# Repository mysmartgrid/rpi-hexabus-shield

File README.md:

rpi-hexabus-shield
==================

This repository contains a plug-in antenna prototype for the raspberry platform.

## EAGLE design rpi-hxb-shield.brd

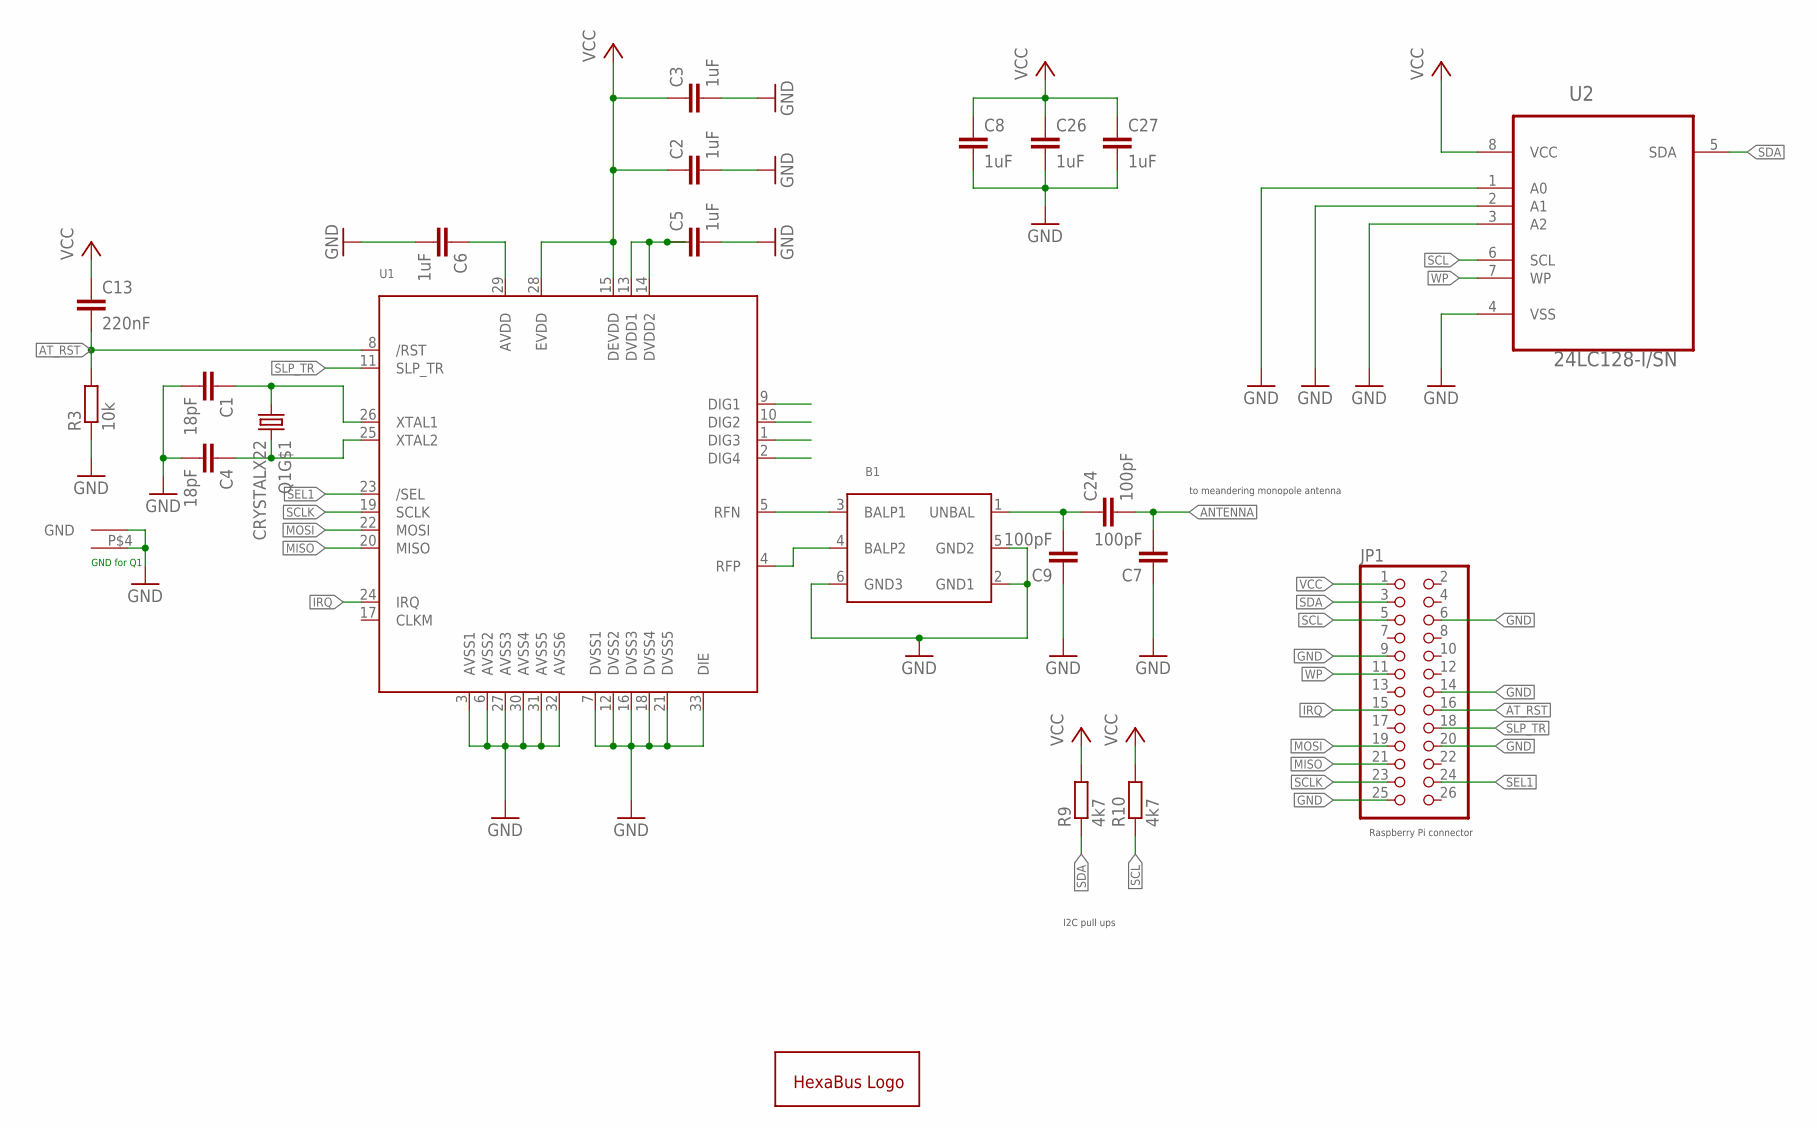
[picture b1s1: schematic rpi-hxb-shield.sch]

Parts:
B1: BALUN+LP; BALUN0805
C1, C4: 18pF; C0402K
C2, C3, C5, C6, C8, C26, C27: 1uF; C0402K
C7, C9, C24: 100pF; C0402K
C13: 220nF; C0402K
JP1: PINHD-2X13; 2X13
Q1: CRYSTALX22; X22
R3: 10k; R0402
R9, R10: 4k7; R0402
U1: AT86RF212; 32QN2
U2: 24LC128-I/SN; SOIC127P600X175-8N
U$1: HEXAKRAKE

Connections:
ANTENNA: C7.2, C24.2
AT_RST: C13.2, JP1.16, R3.2, U1.8 (/RST)
GND: B1.2 (GND1), B1.5 (GND2), B1.6 (GND3), C1.2, C2.2, C3.2, C4.2, C5.2, C6.2, C7.1, C8.2, C9.1, C26.2, C27.2, JP1.6, JP1.9, JP1.14, JP1.20, JP1.25, Q1.P$2 (GND), Q1.P$4 (GND1), R3.1, U1.3 (AVSS1), U1.6 (AVSS2), U1.7 (DVSS1), U1.12 (DVSS2), U1.16 (DVSS3), U1.18 (DVSS4), U1.21 (DVSS5), U1.27 (AVSS3), U1.30 (AVSS4), U1.31 (AVSS5), U1.32 (AVSS6), U1.33 (DIE), U2.1 (A0), U2.2 (A1), U2.3 (A2), U2.4 (VSS)
IRQ: JP1.15, U1.24 (IRQ)
MISO: JP1.21, U1.20 (MISO)
MOSI: JP1.19, U1.22 (MOSI)
unnamed: C6.1, U1.29 (AVDD)
unnamed: C5.1, U1.13 (DVDD1), U1.14 (DVDD2)
unnamed: B1.3 (BALP1), U1.5 (RFN)
unnamed: B1.4 (BALP2), U1.4 (RFP)
unnamed: C1.1, Q1.P$1 (1), U1.26 (XTAL1)
unnamed: C4.1, Q1.P$3 (2), U1.25 (XTAL2)
unnamed: B1.1 (UNBAL), C9.2, C24.1
SCL: JP1.5, R10.1, U2.6 (SCL)
SCLK: JP1.23, U1.19 (SCLK)
SDA: JP1.3, R9.1, U2.5 (SDA)
SEL1: JP1.24, U1.23 (/SEL)
SLP_TR: JP1.18, U1.11 (SLP_TR)
VCC: C2.1, C3.1, C8.1, C13.1, C26.1, C27.1, JP1.1, R9.2, R10.2, U1.15 (DEVDD), U1.28 (EVDD), U2.8 (VCC)
WP: JP1.11, U2.7 (WP)

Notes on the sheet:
GND for Q1
to meandering monopole antenna
I2C pull ups
Raspberry Pi connector

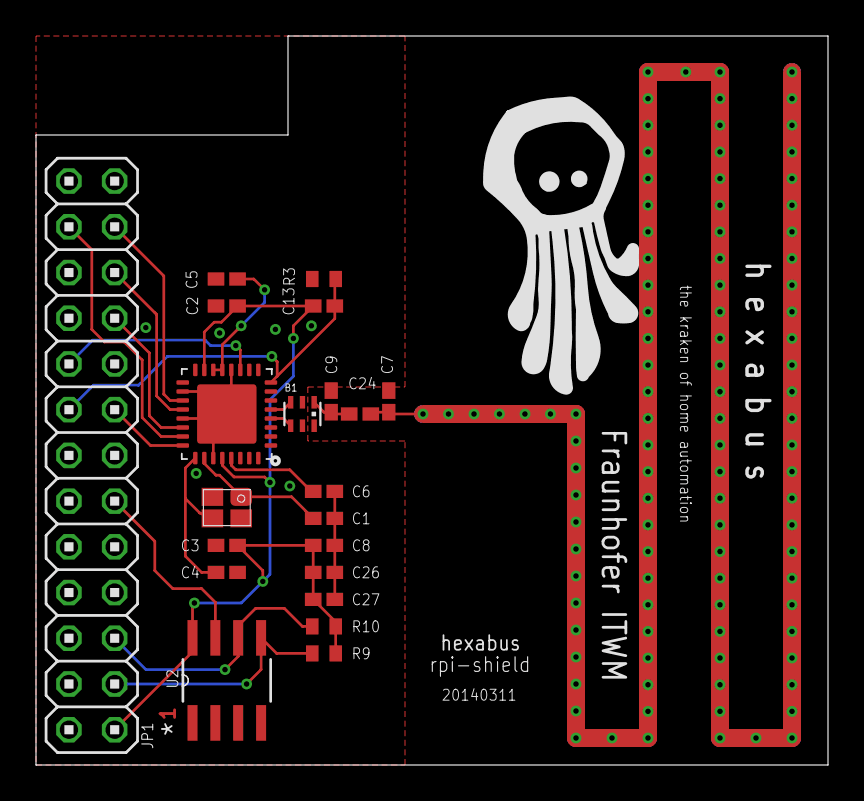
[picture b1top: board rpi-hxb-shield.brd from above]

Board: 2 copper layers, 44.0 x 40.5 mm, 22 parts (0 on the bottom side), 20 nets.

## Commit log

2014-02-04 added gitignore
2014-02-04 added .gitattributes
2014-02-04 imported design files from hxb-devboard and removed unneeded components
2014-02-04 added eeprom for storing mac address and 2x13 pin connector
2014-02-04 renamed design files
2014-02-04 removal of unneeded micromatch connector
2014-02-04 removal of the power LED and ripup of all wires
2014-02-04 swapped EEPROM to 128K variant
2014-02-05 prelimenary routing
2014-02-05 sketch of new layout for accomodation the antenna on the pcb
2014-02-05 EEPOM now with fixed address (hardwired)
2014-02-06 routing
2014-02-06 comments to info layer
2014-02-06 added comments to schematic
2014-02-07 removed CLKM and according resistir
2014-03-04 maximum outline, removed wire antenna
2014-03-05 changed resistors and capacitors to 0402, shuffled parts around
2014-03-06 arranged parts in sort of a grid
2014-03-11 vias for antenna
2014-03-11 fixed overlap issue
2014-03-11 all layers
2014-03-11 added one measurement
2014-03-27 added note for excluded parts
2014-04-01 added BOM
